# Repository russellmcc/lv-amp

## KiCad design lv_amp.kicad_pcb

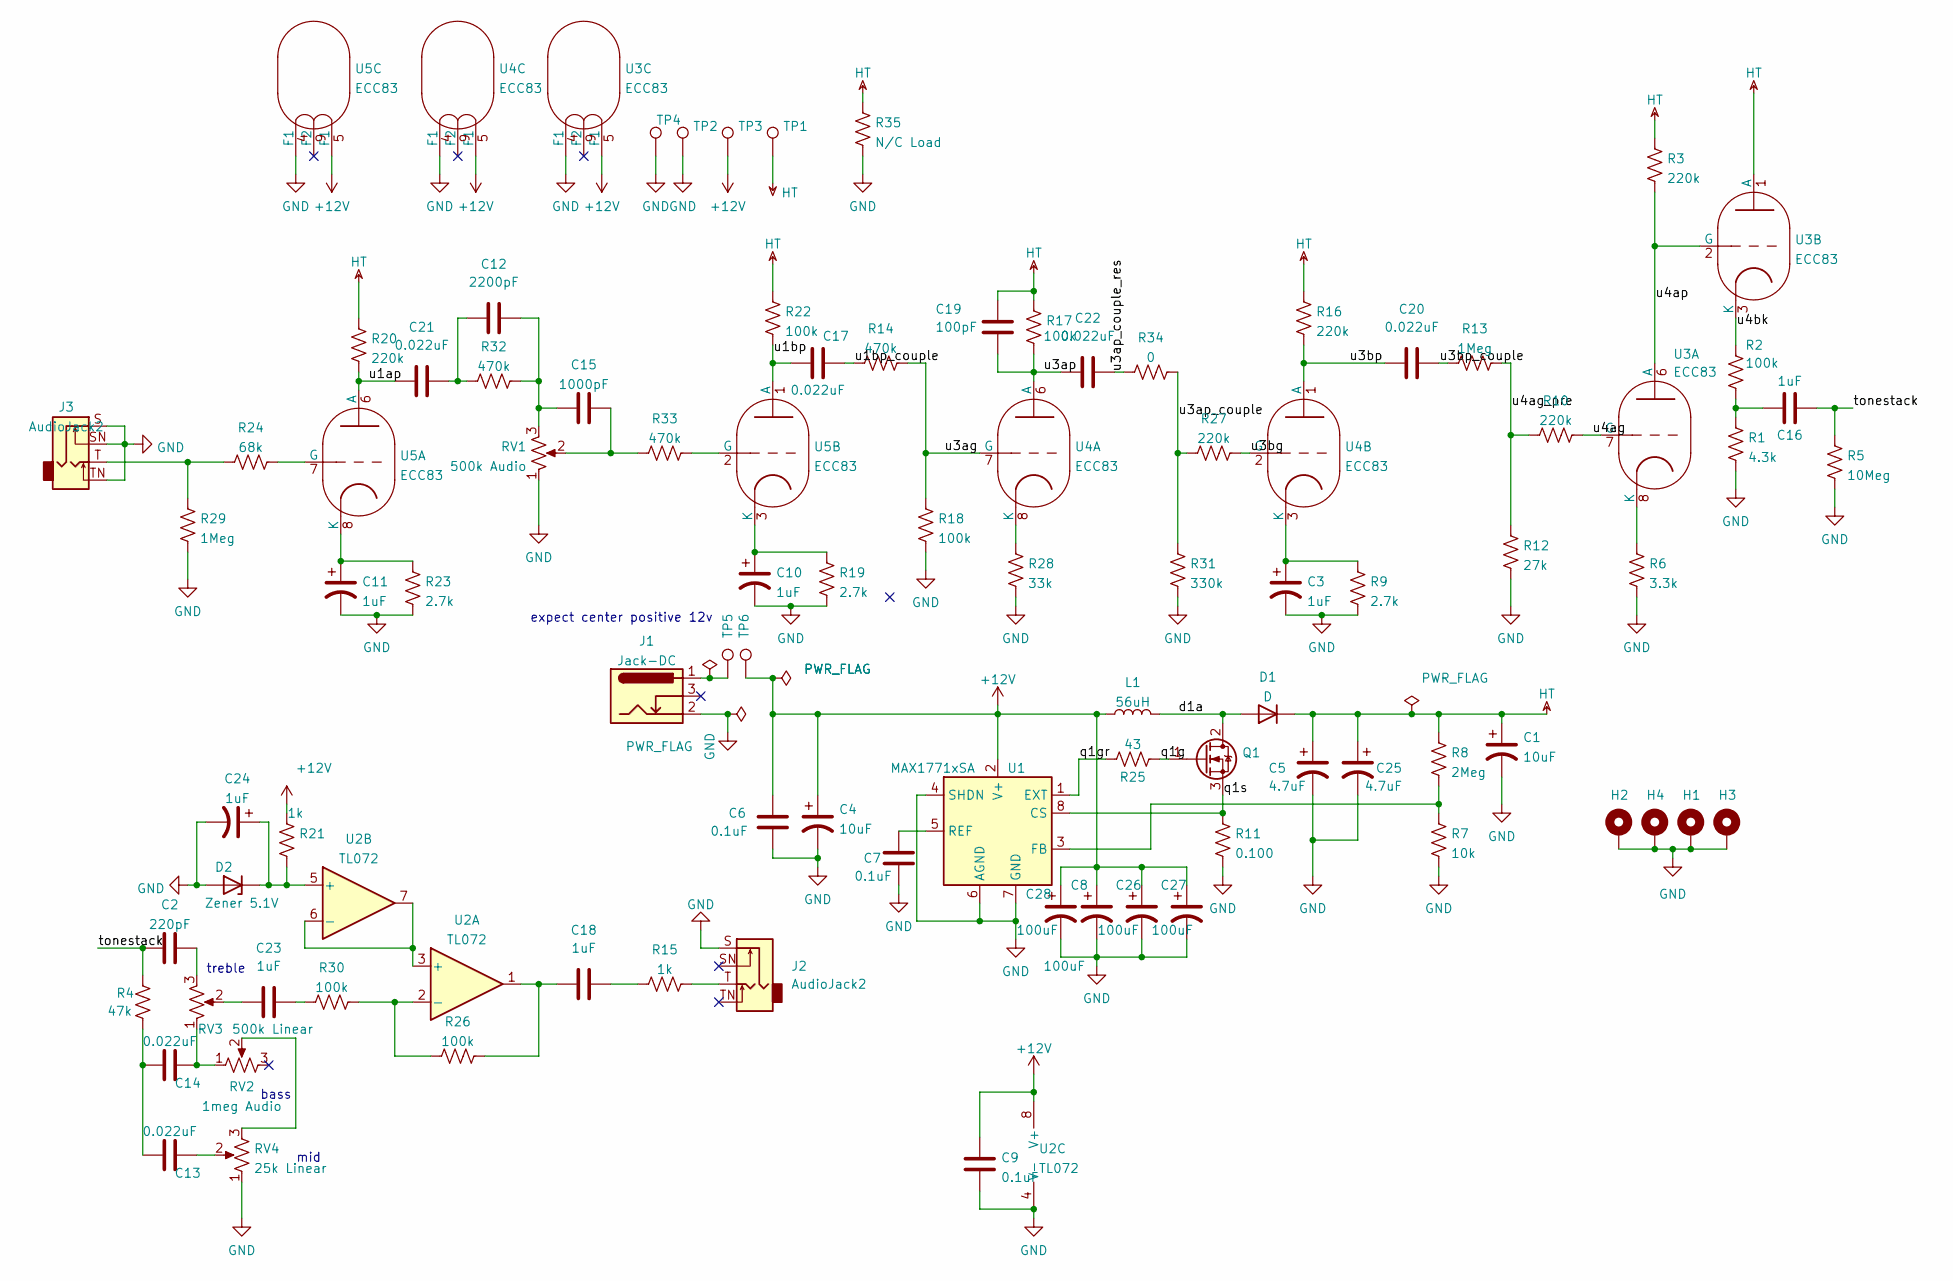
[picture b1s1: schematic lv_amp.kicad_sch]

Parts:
C1: 10uF; CP_Elec_16x17.5
C2: 220pF; C_0603_1608Metric
C3, C10, C11, C24: 1uF; CP_Elec_4x5.4
C4: 10uF; CP_EIA-6032-28_Kemet-C
C5, C25: 4.7uF; CP_Elec_10x10
C6, C7, C9: 0.1uF; C_0805_2012Metric
C8, C26, C27, C28: 100uF; CP_EIA-7343-43_Kemet-X
C12: 2200pF; C_0805_2012Metric
C13, C14: 0.022uF; C_0805_2012Metric
C15: 1000pF; C_0805_2012Metric
C16, C18, C23: 1uF; C_Rect_L18.0mm_W7.0mm_P15.00mm_FKS3_FKP3
C17, C20, C21, C22: 0.022uF; C_Rect_L13.0mm_W4.0mm_P10.00mm_FKS3_FKP3_MKS4
C19: 100pF; C_Rect_L18.0mm_W5.0mm_P15.00mm_FKS3_FKP3
D1: D; TO-263-2_TabPin1
D2: Zener 5.1V; D_SOT-23_ANK
H1, H2, H3, H4: MountingHole_Pad; MountingHole_3.2mm_M3
J1: Jack-DC; Kobiconn 179PH
J2, J3: AudioJack2; Jack_6.35mm_Neutrik_NRJ4HF_Horizontal
L1: 56uH; pm2110
Q1: Q_NMOS_DGS; TO-263-2
R1: 4.3k; R_0603_1608Metric
R2, R17, R22: 100k; R_2512_6332Metric
R3, R10, R16, R20, R27: 220k; R_1210_3225Metric
R4: 47k; R_0603_1608Metric
R5: 10Meg; R_0603_1608Metric
R6: 3.3k; R_1206_3216Metric
R7: 10k; R_0603_1608Metric
R8: 2Meg; R_2512_6332Metric
R9, R19, R23: 2.7k; R_1206_3216Metric
R11: 0.100; R_2512_6332Metric
R12: 27k; R_2512_6332Metric
R13, R29: 1Meg; R_0603_1608Metric
R14, R32, R33: 470k; R_1206_3216Metric
R15, R21: 1k; R_0603_1608Metric
R18, R26, R30: 100k; R_0603_1608Metric
R24: 68k; R_0603_1608Metric
R25: 43; R_0603_1608Metric
R28: 33k; R_0805_2012Metric
R31: 330k; R_1210_3225Metric
R34: 0; R_1210_3225Metric
R35: N/C Load; R_Axial_DIN0309_L9.0mm_D3.2mm_P15.24mm_Horizontal
RV1: 500k Audio; Potentiometer_Piher_T-16H_Single_Horizontal
RV2: 1meg Audio; Potentiometer_Piher_T-16H_Single_Horizontal
RV3: 500k Linear; Potentiometer_Piher_T-16H_Single_Horizontal
RV4: 25k Linear; Potentiometer_Piher_T-16H_Single_Horizontal
TP1, TP2, TP3, TP4, TP5, TP6: TestPoint; TestPoint_THTPad_2.0x2.0mm_Drill1.0mm
U1: MAX1771xSA; SO-8_3.9x4.9mm_P1.27mm
U2: TL072; SO-8_3.9x4.9mm_P1.27mm
U3, U4, U5: ECC83; 12ax7

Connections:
+12V: C4.1, C6.1, C8.1, C9.1, C26.1, C27.1, C28.1, L1.1, R21.1, TP3.1, TP6.1, U1.2 (V+), U2.8 (V+), U3.5 (F1), U4.5 (F1), U5.5 (F1)
/d1a: D1.2 (A), L1.2, Q1.2 (D)
/q1g: Q1.1 (G), R25.2
/q1gr: R25.1, U1.1 (EXT)
/q1s: Q1.3 (S), R11.1, U1.8 (CS)
/tonestack: C2.1, C16.2, R4.2, R5.2
/u1ap: C21.1, R20.2, U5.6 (A)
/u1bp: C17.1, R22.2, U5.1 (A)
/u1bp_couple: C17.2, R14.1
/u3ag: R14.2, R18.2, U4.7 (G)
/u3ap: C19.2, C22.1, R17.2, U4.6 (A)
/u3ap_couple: R27.1, R31.2, R34.1
/u3ap_couple_res: C22.2, R34.2
/u3bg: R27.2, U4.2 (G)
/u3bp: C20.1, R16.2, U4.1 (A)
/u3bp_couple: C20.2, R13.1
/u4ag: R10.2, U3.7 (G)
/u4ag_pre: R10.1, R12.2, R13.2
/u4ap: R3.2, U3.2 (G), U3.6 (A)
/u4bk: R2.1, U3.3 (K)
GND: C1.2, C3.2, C4.2, C5.2, C6.2, C7.2, C8.2, C9.2, C10.2, C11.2, C24.2, C25.2, C26.2, C27.2, C28.2, D2.2 (A), H1.1, H2.1, H3.1, H4.1, J1.2, J2.S, J3.S, J3.SN, J3.TN, R1.2, R5.1, R6.2, R7.2, R9.2, R11.2, R12.1, R18.1, R19.2, R23.2, R28.1, R29.2, R31.1, R35.2, RV1.1, RV4.1, TP2.1, TP4.1, U1.4 (SHDN), U1.6 (AGND), U1.7 (GND), U2.4 (V-), U3.4 (F1), U4.4 (F1), U5.4 (F1)
HT: C1.1, C5.1, C19.1, C25.1, D1.1 (K), R3.1, R8.1, R16.1, R17.1, R20.1, R22.1, R35.1, TP1.1, U3.1 (A)
unnamed: C2.2, RV3.3
unnamed: C12.1, C21.2, R32.1
unnamed: C12.2, C15.1, R32.2, RV1.3
unnamed: C13.1, C14.1, R4.1
unnamed: C13.2, RV4.2
unnamed: C14.2, RV2.1, RV3.1
unnamed: C15.2, R33.1, RV1.2
unnamed: C16.1, R1.1, R2.2
unnamed: C18.1, R26.1, U2.1
unnamed: C18.2, R15.2
unnamed: C23.1, RV3.2
unnamed: C23.2, R30.2
unnamed: C24.1, D2.1 (K), R21.2, U2.5 (+)
unnamed: J1.1, TP5.1
unnamed: J2.T, R15.1
unnamed: J3.T, R24.2, R29.1
unnamed: RV2.2, RV4.3
unnamed: R7.1, R8.2, U1.3 (FB)
unnamed: C7.1, U1.5 (REF)
unnamed: U2.3 (+), U2.6 (-), U2.7
unnamed: R26.2, R30.1, U2.2 (-)
unnamed: R6.1, U3.8 (K)
unnamed: R28.2, U4.8 (K)
unnamed: C3.1, R9.1, U4.3 (K)
unnamed: R24.1, U5.7 (G)
unnamed: C11.1, R23.1, U5.8 (K)
unnamed: R33.2, U5.2 (G)
unnamed: C10.1, R19.1, U5.3 (K)

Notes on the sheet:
treble
expect center positive 12v
mid
bass

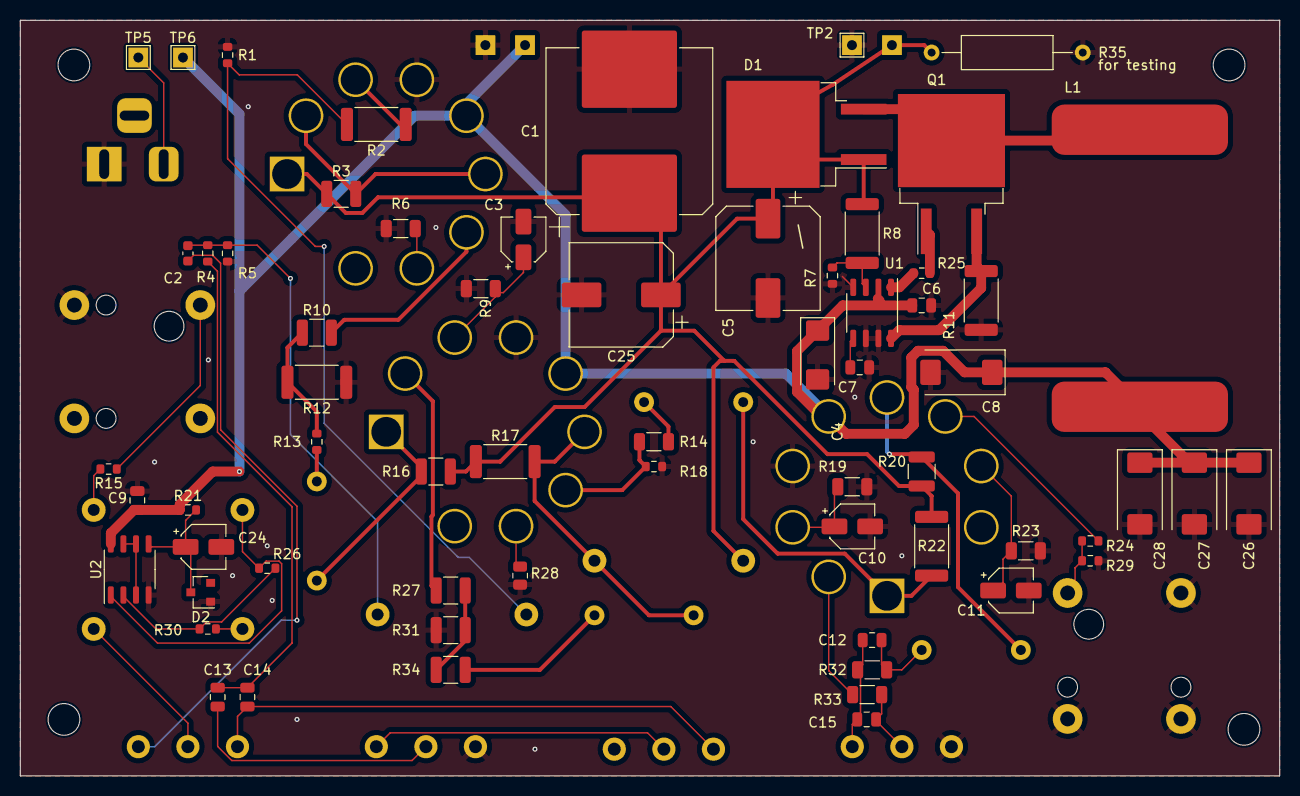
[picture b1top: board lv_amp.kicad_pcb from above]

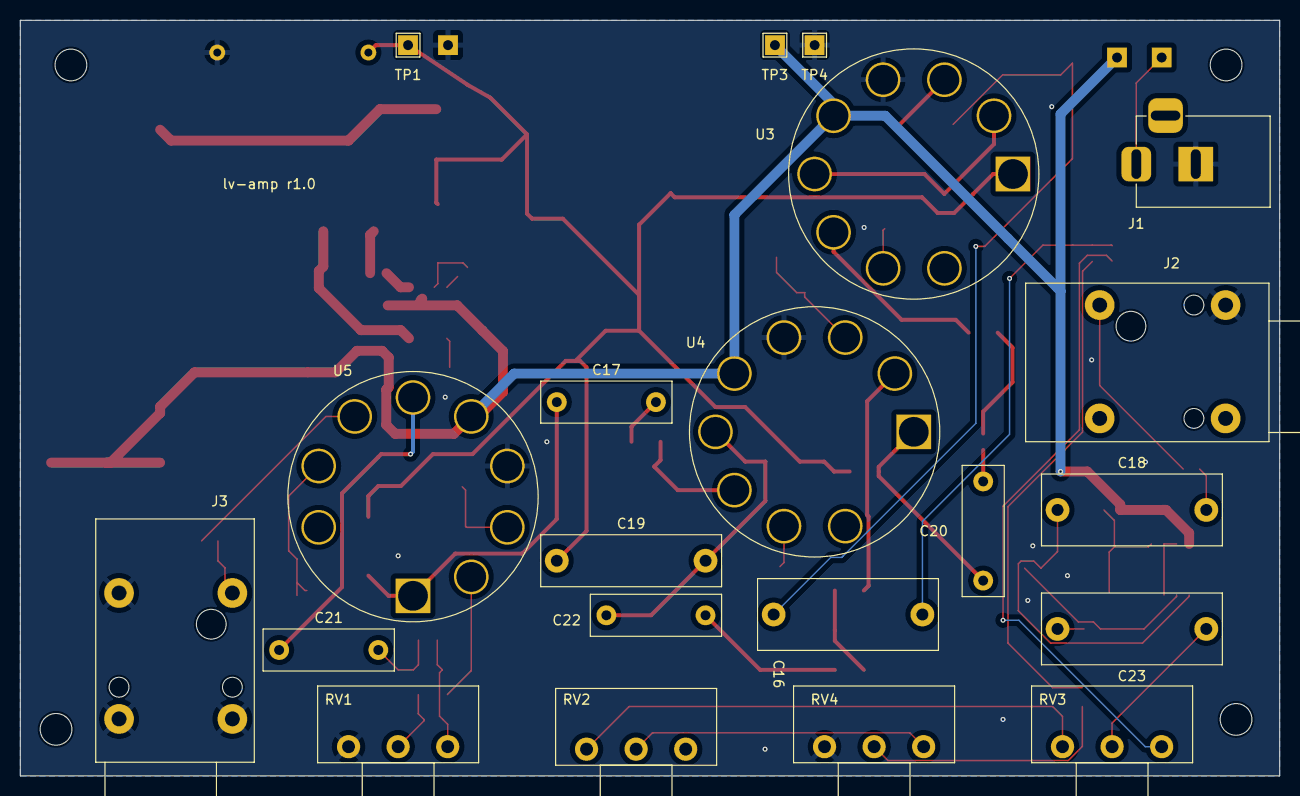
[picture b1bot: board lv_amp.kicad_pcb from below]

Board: 2 copper layers, 127.0 x 76.2 mm, 89 parts (21 on the bottom side), 50 nets.

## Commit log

2022-02-21 initial
2022-02-21 power supply parts
2022-02-21 update footprints
2022-02-21 caps
2022-02-21 footprints
2022-02-21 add net classes
2022-02-21 power supply layout
2022-02-21 initial layout
2022-02-21 tighter layout
2022-02-21 flipsies
2022-02-21 route/re-annotate
2022-02-21 tweaks
2022-02-21 alpha0 errata: dd zener diode to output reference
2022-02-21 alpha0 errata: add gate resistor for switching mosfet
2022-02-21 alpha0 errata: DC jack
2022-02-21 alpha0 errata: better output filtering on supply
2022-02-21 alpha0 errata: more input filtering on inductor
2022-02-21 alpha0 errata: add 0ohm resistor for easier modding of stage 4
2022-02-21 alpha1 complete
2022-02-21 finish errata from alpha0
2022-02-21 alpha0 errata: decrease r12 to 27k to reduce stage 5 gain
2022-02-21 alpha0 errata: reduce R18 to reduce stage 4 gain
2022-02-21 alpha0 errata: note taper for pots
2022-02-21 alpha0 errata: add slot for load resistor for testing
2022-02-21 alpha0 errata: increase r1 to 4.3k to increase output level
2022-02-21 alpha0 errata: flip mid pot
2022-02-21 gitignore
2022-02-21 shuffle stuff around to minimize antenna length
2022-02-21 5v zener
2022-02-21 use 5.1 zener
2022-02-21 Fix vendor links
2022-02-27 Oops un-flip mid pot
2022-02-27 Errata: flip pot order
2025-04-13 errata - add power switch
2025-04-13 power switch on hot side; fix drc fails in new version
